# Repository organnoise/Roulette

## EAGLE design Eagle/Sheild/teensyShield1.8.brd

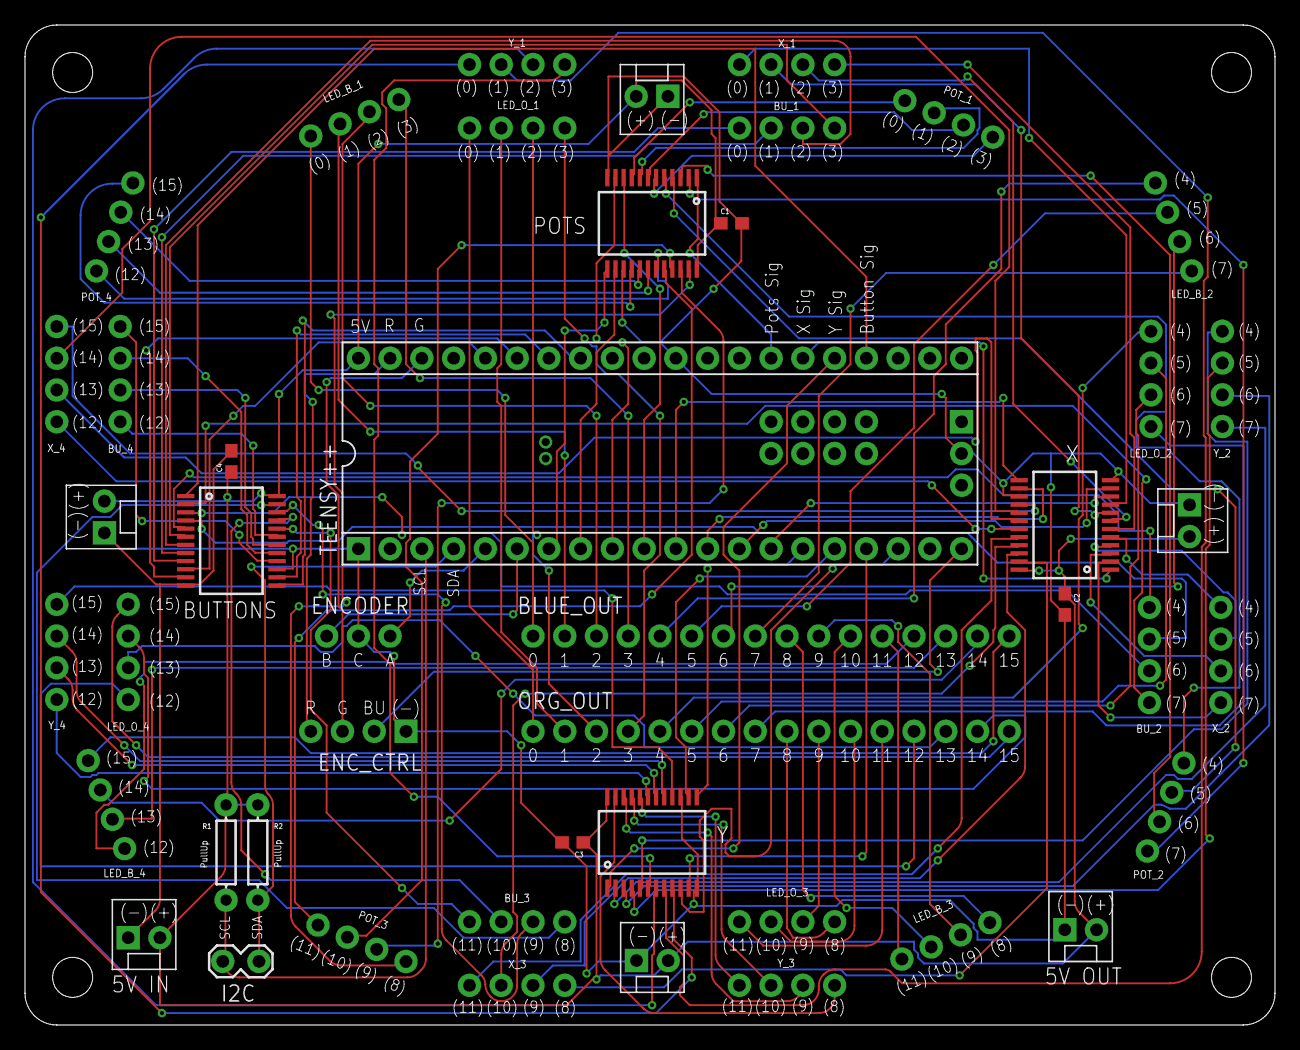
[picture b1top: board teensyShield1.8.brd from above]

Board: 2 copper layers, 100.0 x 80.0 mm, 46 parts (0 on the bottom side), 125 nets.

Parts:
BLUE_OUT: 1X16_NO_SILK
BUTTONS: MUX-74HC4067; SSOP24
BU_1, BU_2, BU_3, BU_4: 1X04_NO_SILK_ALL_ROUND
C1, C2, C3, C4: 0.1uF; 0603
ENCODER: 1X03_NO_SILK
ENC_CTRL: 1X04_NO_SILK
I2C: 1X02_LOCK
LED_B_1, LED_B_2, LED_B_3, LED_B_4: 1X04_NO_SILK_ALL_ROUND
LED_O_1, LED_O_2, LED_O_3, LED_O_4: 1X04_NO_SILK_ALL_ROUND
ORG_OUT: 1X16_NO_SILK
POTS: MUX-74HC4067; SSOP24
POT_1, POT_2, POT_3, POT_4: 1X04_NO_SILK_ALL_ROUND
POW_1, POW_2, POW_3, POW_4: MOLEX-1X2
POW_IN: MOLEX-1X2
POW_OUT: MOLEX-1X2
R1, R2: PullUp; AXIAL-0.3
TEENSY++: ARDUINO-TEENSY++; TEENSY++
X: MUX-74HC4067; SSOP24
X_1, X_2, X_3, X_4: 1X04_NO_SILK_ALL_ROUND
Y: MUX-74HC4067; SSOP24
Y_1, Y_2, Y_3, Y_4: 1X04_NO_SILK_ALL_ROUND

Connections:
5V: BUTTONS.24, C1.1, C2.1, C3.1, C4.1, POTS.24, POW_1.2, POW_2.2, POW_3.2, POW_4.2, POW_IN.2, POW_OUT.2, R1.P$2, R2.P$1, TEENSY++.+5V, X.24, Y.24
BU_C0: BUTTONS.9, BU_1.1
BU_C1: BUTTONS.8, BU_1.2
BU_C2: BUTTONS.7, BU_1.3
BU_C3: BUTTONS.6, BU_1.4
BU_C4: BUTTONS.5, BU_2.1
BU_C5: BUTTONS.4, BU_2.2
BU_C6: BUTTONS.3, BU_2.3
BU_C7: BUTTONS.2, BU_2.4
BU_C8: BUTTONS.23, BU_3.1
BU_C9: BUTTONS.22, BU_3.2
BU_C10: BUTTONS.21, BU_3.3
BU_C11: BUTTONS.20, BU_3.4
BU_C12: BUTTONS.19, BU_4.1
BU_C13: BUTTONS.18, BU_4.2
BU_C14: BUTTONS.17, BU_4.3
BU_C15: BUTTONS.16, BU_4.4
ENC_1: ENCODER.3, TEENSY++.D2
ENC_2: ENCODER.1, TEENSY++.D3
ENC_BU: ENC_CTRL.2, TEENSY++.C7
ENC_G: ENC_CTRL.3, TEENSY++.B5
ENC_R: ENC_CTRL.4, TEENSY++.B6
GND: BUTTONS.12, BUTTONS.15, C1.2, C2.2, C3.2, C4.2, ENCODER.2, ENC_CTRL.1, POTS.12, POTS.15, POW_1.1, POW_2.1, POW_3.1, POW_4.1, POW_IN.1, POW_OUT.1, TEENSY++.GND, TEENSY++.GND2, TEENSY++.GRND1, X.12, X.15, Y.12, Y.15
LED_B_C0: BLUE_OUT.1, LED_B_1.1
LED_B_C1: BLUE_OUT.2, LED_B_1.2
LED_B_C2: BLUE_OUT.3, LED_B_1.3
LED_B_C3: BLUE_OUT.4, LED_B_1.4
LED_B_C4: BLUE_OUT.5, LED_B_2.1
LED_B_C5: BLUE_OUT.6, LED_B_2.2
LED_B_C6: BLUE_OUT.7, LED_B_2.3
LED_B_C7: BLUE_OUT.8, LED_B_2.4
LED_B_C8: BLUE_OUT.9, LED_B_3.1
LED_B_C9: BLUE_OUT.10, LED_B_3.2
LED_B_C10: BLUE_OUT.11, LED_B_3.3
LED_B_C11: BLUE_OUT.12, LED_B_3.4
LED_B_C12: BLUE_OUT.13, LED_B_4.1
LED_B_C13: BLUE_OUT.14, LED_B_4.2
LED_B_C14: BLUE_OUT.15, LED_B_4.3
LED_B_C15: BLUE_OUT.16, LED_B_4.4
LED_O_C0: LED_O_1.1, ORG_OUT.1
LED_O_C1: LED_O_1.2, ORG_OUT.2
LED_O_C2: LED_O_1.3, ORG_OUT.3
LED_O_C3: LED_O_1.4, ORG_OUT.4
LED_O_C4: LED_O_2.1, ORG_OUT.5
LED_O_C5: LED_O_2.2, ORG_OUT.6
LED_O_C6: LED_O_2.3, ORG_OUT.7
LED_O_C7: LED_O_2.4, ORG_OUT.8
LED_O_C8: LED_O_3.1, ORG_OUT.9
LED_O_C9: LED_O_3.2, ORG_OUT.10
LED_O_C10: LED_O_3.3, ORG_OUT.11
LED_O_C11: LED_O_3.4, ORG_OUT.12
LED_O_C12: LED_O_4.1, ORG_OUT.13
LED_O_C13: LED_O_4.2, ORG_OUT.14
LED_O_C14: LED_O_4.3, ORG_OUT.15
LED_O_C15: LED_O_4.4, ORG_OUT.16
MUX1_S0: POTS.10, TEENSY++.D7
MUX1_S1: POTS.11, TEENSY++.D6
MUX1_S2: POTS.14, TEENSY++.D5
MUX1_S3: POTS.13, TEENSY++.D4
MUX1_SIG: POTS.1, TEENSY++.F1
MUX2_S0: TEENSY++.C1, X.10
MUX2_S1: TEENSY++.C0, X.11
MUX2_S2: TEENSY++.E1, X.14
MUX2_S3: TEENSY++.E0, X.13
MUX2_SIG: TEENSY++.F2, X.1
MUX3_S0: TEENSY++.C5, Y.10
MUX3_S1: TEENSY++.C4, Y.11
MUX3_S2: TEENSY++.C3, Y.14
MUX3_S3: TEENSY++.C2, Y.13
MUX3_SIG: TEENSY++.F3, Y.1
MUX4_S0: BUTTONS.10, TEENSY++.B3
MUX4_S1: BUTTONS.11, TEENSY++.B2
MUX4_S2: BUTTONS.14, TEENSY++.B1
MUX4_S3: BUTTONS.13, TEENSY++.B0
MUX4_SIG: BUTTONS.1, TEENSY++.F4
POT_C0: POTS.9, POT_1.1
POT_C1: POTS.8, POT_1.2
POT_C2: POTS.7, POT_1.3
POT_C3: POTS.6, POT_1.4
POT_C4: POTS.5, POT_2.1
POT_C5: POTS.4, POT_2.2
POT_C6: POTS.3, POT_2.3
POT_C7: POTS.2, POT_2.4
POT_C8: POTS.23, POT_3.1
POT_C9: POTS.22, POT_3.2
POT_C10: POTS.21, POT_3.3
POT_C11: POTS.20, POT_3.4
POT_C12: POTS.19, POT_4.1
POT_C13: POTS.18, POT_4.2
POT_C14: POTS.17, POT_4.3
POT_C15: POTS.16, POT_4.4
SCL: I2C.2, R1.P$1, TEENSY++.D0
SDA: I2C.1, R2.P$2, TEENSY++.D1
X_C0: X.9, X_1.1
X_C1: X.8, X_1.2
X_C2: X.7, X_1.3
X_C3: X.6, X_1.4
X_C4: X.5, X_2.1
X_C5: X.4, X_2.2
X_C6: X.3, X_2.3
X_C7: X.2, X_2.4
X_C8: X.23, X_3.1
X_C9: X.22, X_3.2
X_C10: X.21, X_3.3
X_C11: X.20, X_3.4
X_C12: X.19, X_4.1
X_C13: X.18, X_4.2
X_C14: X.17, X_4.3
X_C15: X.16, X_4.4
Y_C0: Y.9, Y_1.1
Y_C1: Y.8, Y_1.2
Y_C2: Y.7, Y_1.3
Y_C3: Y.6, Y_1.4
Y_C4: Y.5, Y_2.1
Y_C5: Y.4, Y_2.2
Y_C6: Y.3, Y_2.3
Y_C7: Y.2, Y_2.4
Y_C8: Y.23, Y_3.1
Y_C9: Y.22, Y_3.2
Y_C10: Y.21, Y_3.3
Y_C11: Y.20, Y_3.4
Y_C12: Y.19, Y_4.1
Y_C13: Y.18, Y_4.2
Y_C14: Y.17, Y_4.3
Y_C15: Y.16, Y_4.4

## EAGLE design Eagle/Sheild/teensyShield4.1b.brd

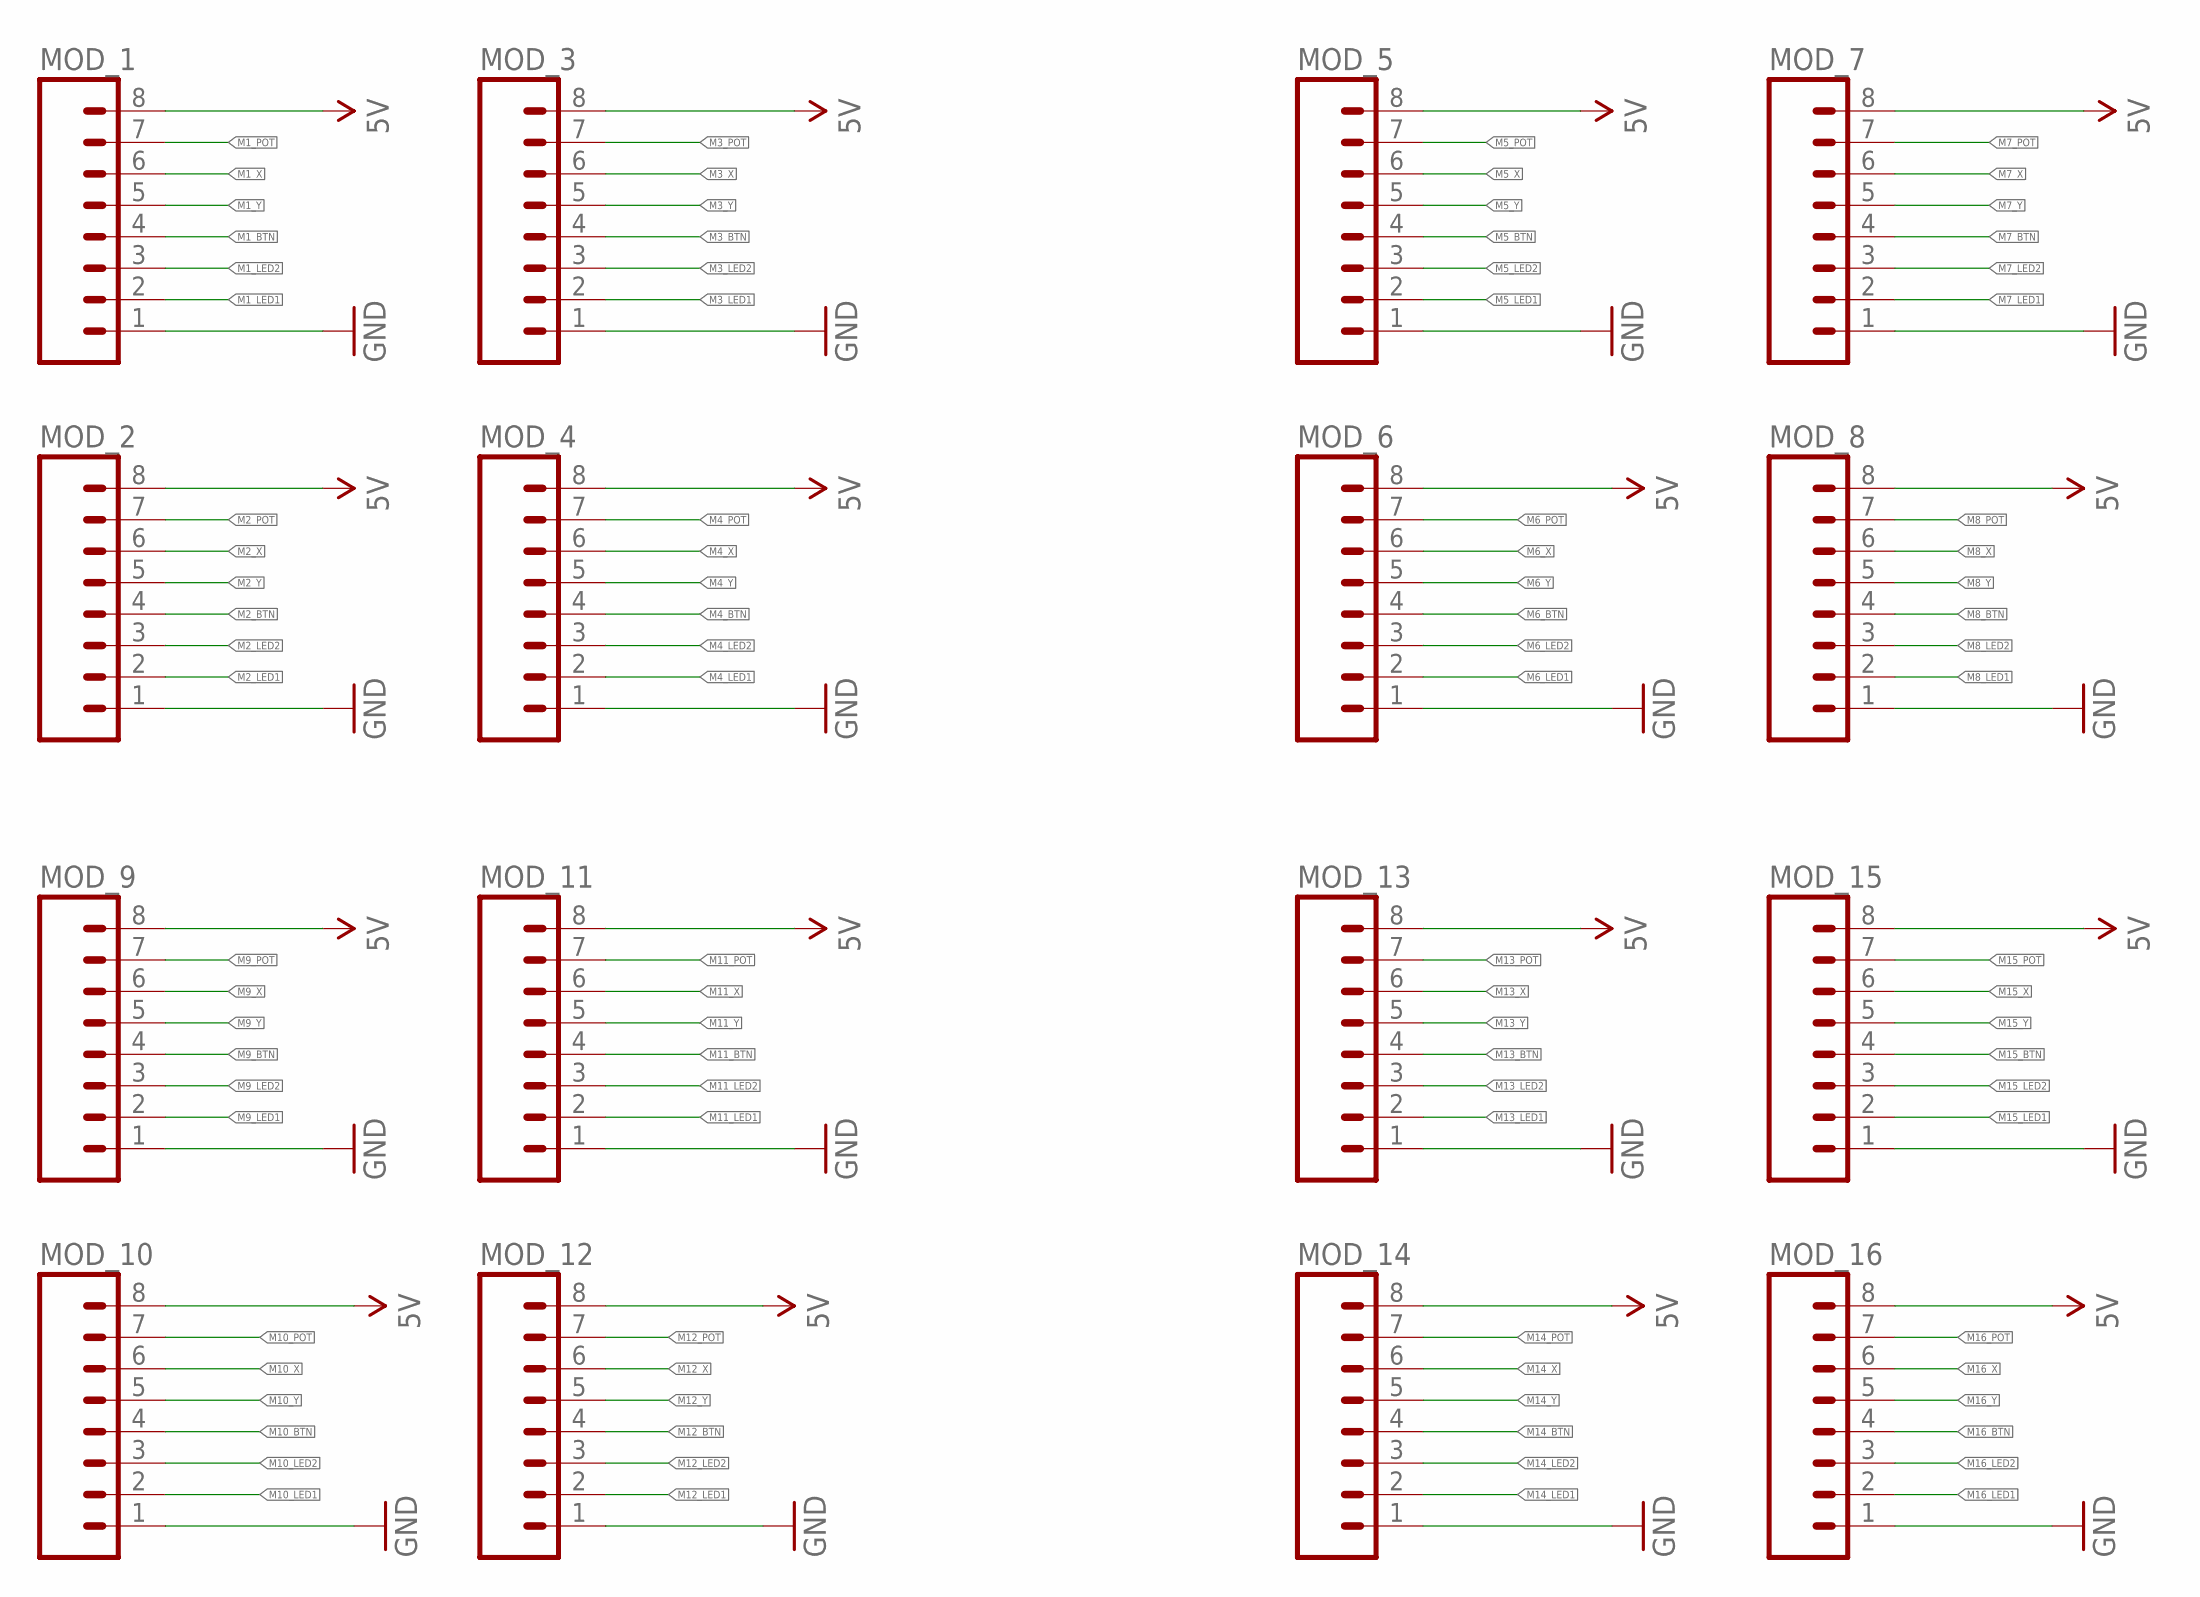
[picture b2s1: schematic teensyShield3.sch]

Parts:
MOD_1, MOD_2, MOD_3, MOD_4, MOD_5, MOD_6, MOD_7, MOD_8, MOD_9, MOD_10, MOD_11, MOD_12, MOD_13, MOD_14, MOD_15, MOD_16: M08; 1X08_ROUND

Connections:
5V: MOD_1.8, MOD_2.8, MOD_3.8, MOD_4.8, MOD_5.8, MOD_6.8, MOD_7.8, MOD_8.8, MOD_9.8, MOD_10.8, MOD_11.8, MOD_12.8, MOD_13.8, MOD_14.8, MOD_15.8, MOD_16.8; also elsewhere on the board
GND: MOD_1.1, MOD_2.1, MOD_3.1, MOD_4.1, MOD_5.1, MOD_6.1, MOD_7.1, MOD_8.1, MOD_9.1, MOD_10.1, MOD_11.1, MOD_12.1, MOD_13.1, MOD_14.1, MOD_15.1, MOD_16.1; also elsewhere on the board
M1_BTN: MOD_1.4; also elsewhere on the board
M1_LED1: MOD_1.2; also elsewhere on the board
M1_LED2: MOD_1.3; also elsewhere on the board
M1_POT: MOD_1.7; also elsewhere on the board
M1_X: MOD_1.6; also elsewhere on the board
M1_Y: MOD_1.5; also elsewhere on the board
M2_BTN: MOD_2.4; also elsewhere on the board
M2_LED1: MOD_2.2; also elsewhere on the board
M2_LED2: MOD_2.3; also elsewhere on the board
M2_POT: MOD_2.7; also elsewhere on the board
M2_X: MOD_2.6; also elsewhere on the board
M2_Y: MOD_2.5; also elsewhere on the board
M3_BTN: MOD_3.4; also elsewhere on the board
M3_LED1: MOD_3.2; also elsewhere on the board
M3_LED2: MOD_3.3; also elsewhere on the board
M3_POT: MOD_3.7; also elsewhere on the board
M3_X: MOD_3.6; also elsewhere on the board
M3_Y: MOD_3.5; also elsewhere on the board
M4_BTN: MOD_4.4; also elsewhere on the board
M4_LED1: MOD_4.2; also elsewhere on the board
M4_LED2: MOD_4.3; also elsewhere on the board
M4_POT: MOD_4.7; also elsewhere on the board
M4_X: MOD_4.6; also elsewhere on the board
M4_Y: MOD_4.5; also elsewhere on the board
M5_BTN: MOD_5.4; also elsewhere on the board
M5_LED1: MOD_5.2; also elsewhere on the board
M5_LED2: MOD_5.3; also elsewhere on the board
M5_POT: MOD_5.7; also elsewhere on the board
M5_X: MOD_5.6; also elsewhere on the board
M5_Y: MOD_5.5; also elsewhere on the board
M6_BTN: MOD_6.4; also elsewhere on the board
M6_LED1: MOD_6.2; also elsewhere on the board
M6_LED2: MOD_6.3; also elsewhere on the board
M6_POT: MOD_6.7; also elsewhere on the board
M6_X: MOD_6.6; also elsewhere on the board
M6_Y: MOD_6.5; also elsewhere on the board
M7_BTN: MOD_7.4; also elsewhere on the board
M7_LED1: MOD_7.2; also elsewhere on the board
M7_LED2: MOD_7.3; also elsewhere on the board
M7_POT: MOD_7.7; also elsewhere on the board
M7_X: MOD_7.6; also elsewhere on the board
M7_Y: MOD_7.5; also elsewhere on the board
M8_BTN: MOD_8.4; also elsewhere on the board
M8_LED1: MOD_8.2; also elsewhere on the board
M8_LED2: MOD_8.3; also elsewhere on the board
M8_POT: MOD_8.7; also elsewhere on the board
M8_X: MOD_8.6; also elsewhere on the board
M8_Y: MOD_8.5; also elsewhere on the board
M9_BTN: MOD_9.4; also elsewhere on the board
M9_LED1: MOD_9.2; also elsewhere on the board
M9_LED2: MOD_9.3; also elsewhere on the board
M9_POT: MOD_9.7; also elsewhere on the board
M9_X: MOD_9.6; also elsewhere on the board
M9_Y: MOD_9.5; also elsewhere on the board
M10_BTN: MOD_10.4; also elsewhere on the board
M10_LED1: MOD_10.2; also elsewhere on the board
M10_LED2: MOD_10.3; also elsewhere on the board
M10_POT: MOD_10.7; also elsewhere on the board
M10_X: MOD_10.6; also elsewhere on the board
M10_Y: MOD_10.5; also elsewhere on the board
M11_BTN: MOD_11.4; also elsewhere on the board
M11_LED1: MOD_11.2; also elsewhere on the board
M11_LED2: MOD_11.3; also elsewhere on the board
M11_POT: MOD_11.7; also elsewhere on the board
M11_X: MOD_11.6; also elsewhere on the board
M11_Y: MOD_11.5; also elsewhere on the board
M12_BTN: MOD_12.4; also elsewhere on the board
M12_LED1: MOD_12.2; also elsewhere on the board
M12_LED2: MOD_12.3; also elsewhere on the board
M12_POT: MOD_12.7; also elsewhere on the board
M12_X: MOD_12.6; also elsewhere on the board
M12_Y: MOD_12.5; also elsewhere on the board
M13_BTN: MOD_13.4; also elsewhere on the board
M13_LED1: MOD_13.2; also elsewhere on the board
M13_LED2: MOD_13.3; also elsewhere on the board
M13_POT: MOD_13.7; also elsewhere on the board
M13_X: MOD_13.6; also elsewhere on the board
M13_Y: MOD_13.5; also elsewhere on the board
M14_BTN: MOD_14.4; also elsewhere on the board
M14_LED1: MOD_14.2; also elsewhere on the board
M14_LED2: MOD_14.3; also elsewhere on the board
M14_POT: MOD_14.7; also elsewhere on the board
M14_X: MOD_14.6; also elsewhere on the board
M14_Y: MOD_14.5; also elsewhere on the board
M15_BTN: MOD_15.4; also elsewhere on the board
M15_LED1: MOD_15.2; also elsewhere on the board
M15_LED2: MOD_15.3; also elsewhere on the board
M15_POT: MOD_15.7; also elsewhere on the board
M15_X: MOD_15.6; also elsewhere on the board
M15_Y: MOD_15.5; also elsewhere on the board
M16_BTN: MOD_16.4; also elsewhere on the board
M16_LED1: MOD_16.2; also elsewhere on the board
M16_LED2: MOD_16.3; also elsewhere on the board
M16_POT: MOD_16.7; also elsewhere on the board
M16_X: MOD_16.6; also elsewhere on the board
M16_Y: MOD_16.5; also elsewhere on the board

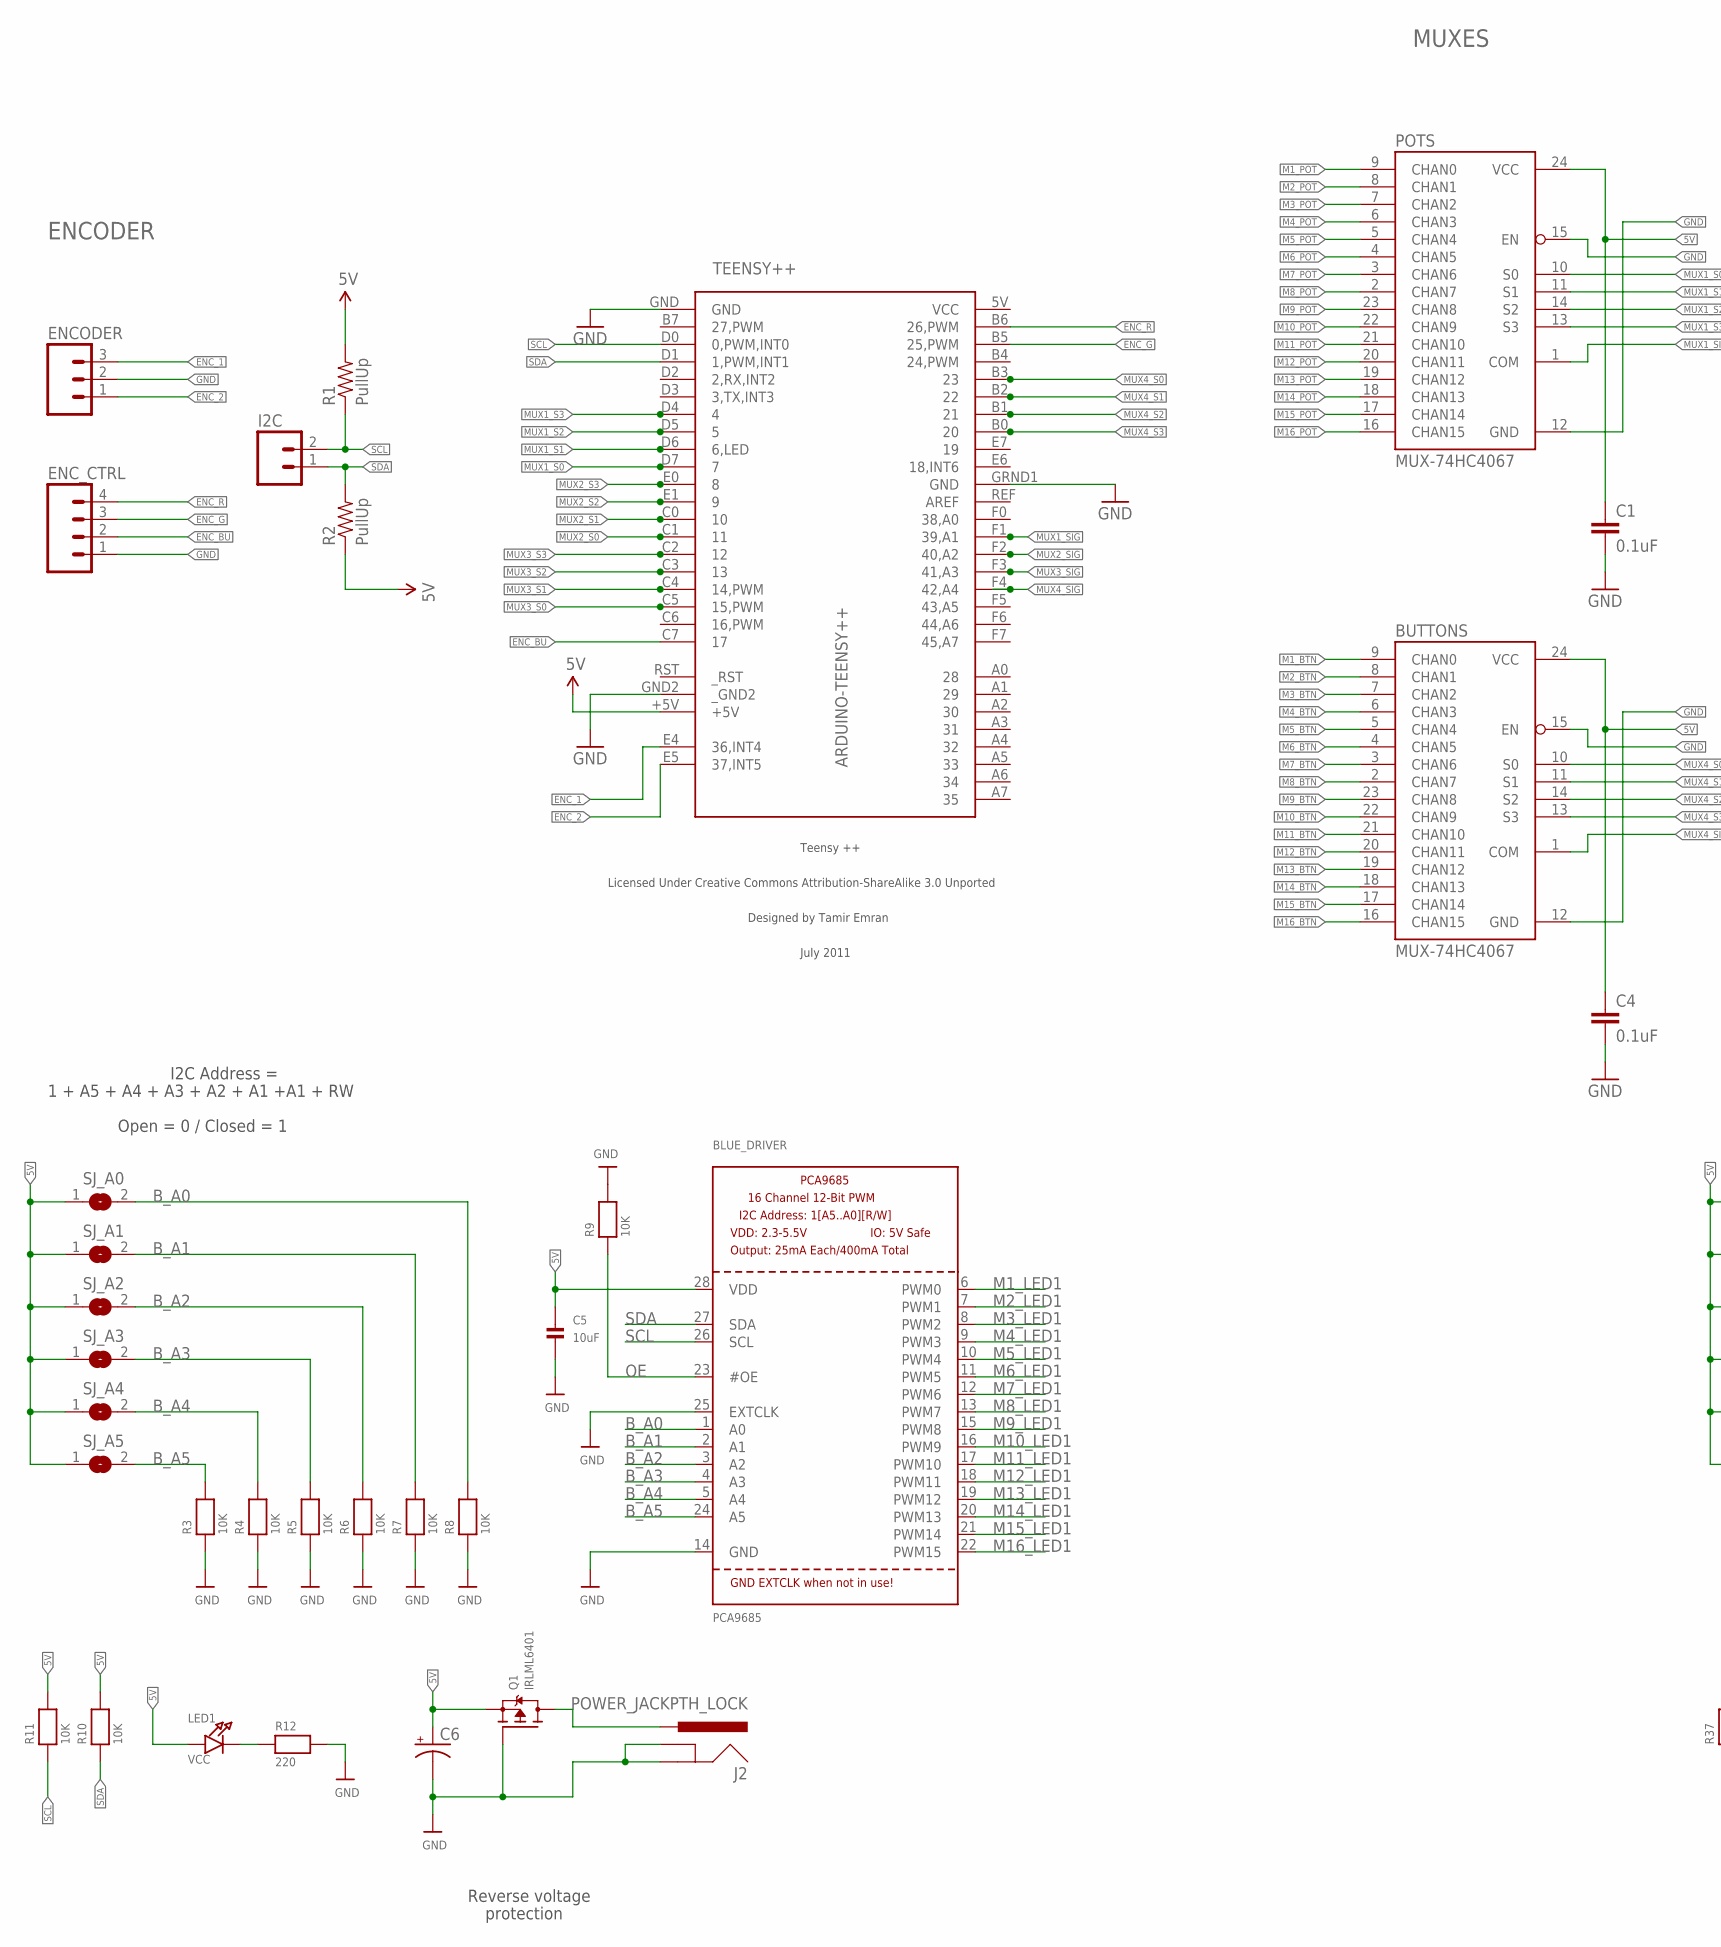
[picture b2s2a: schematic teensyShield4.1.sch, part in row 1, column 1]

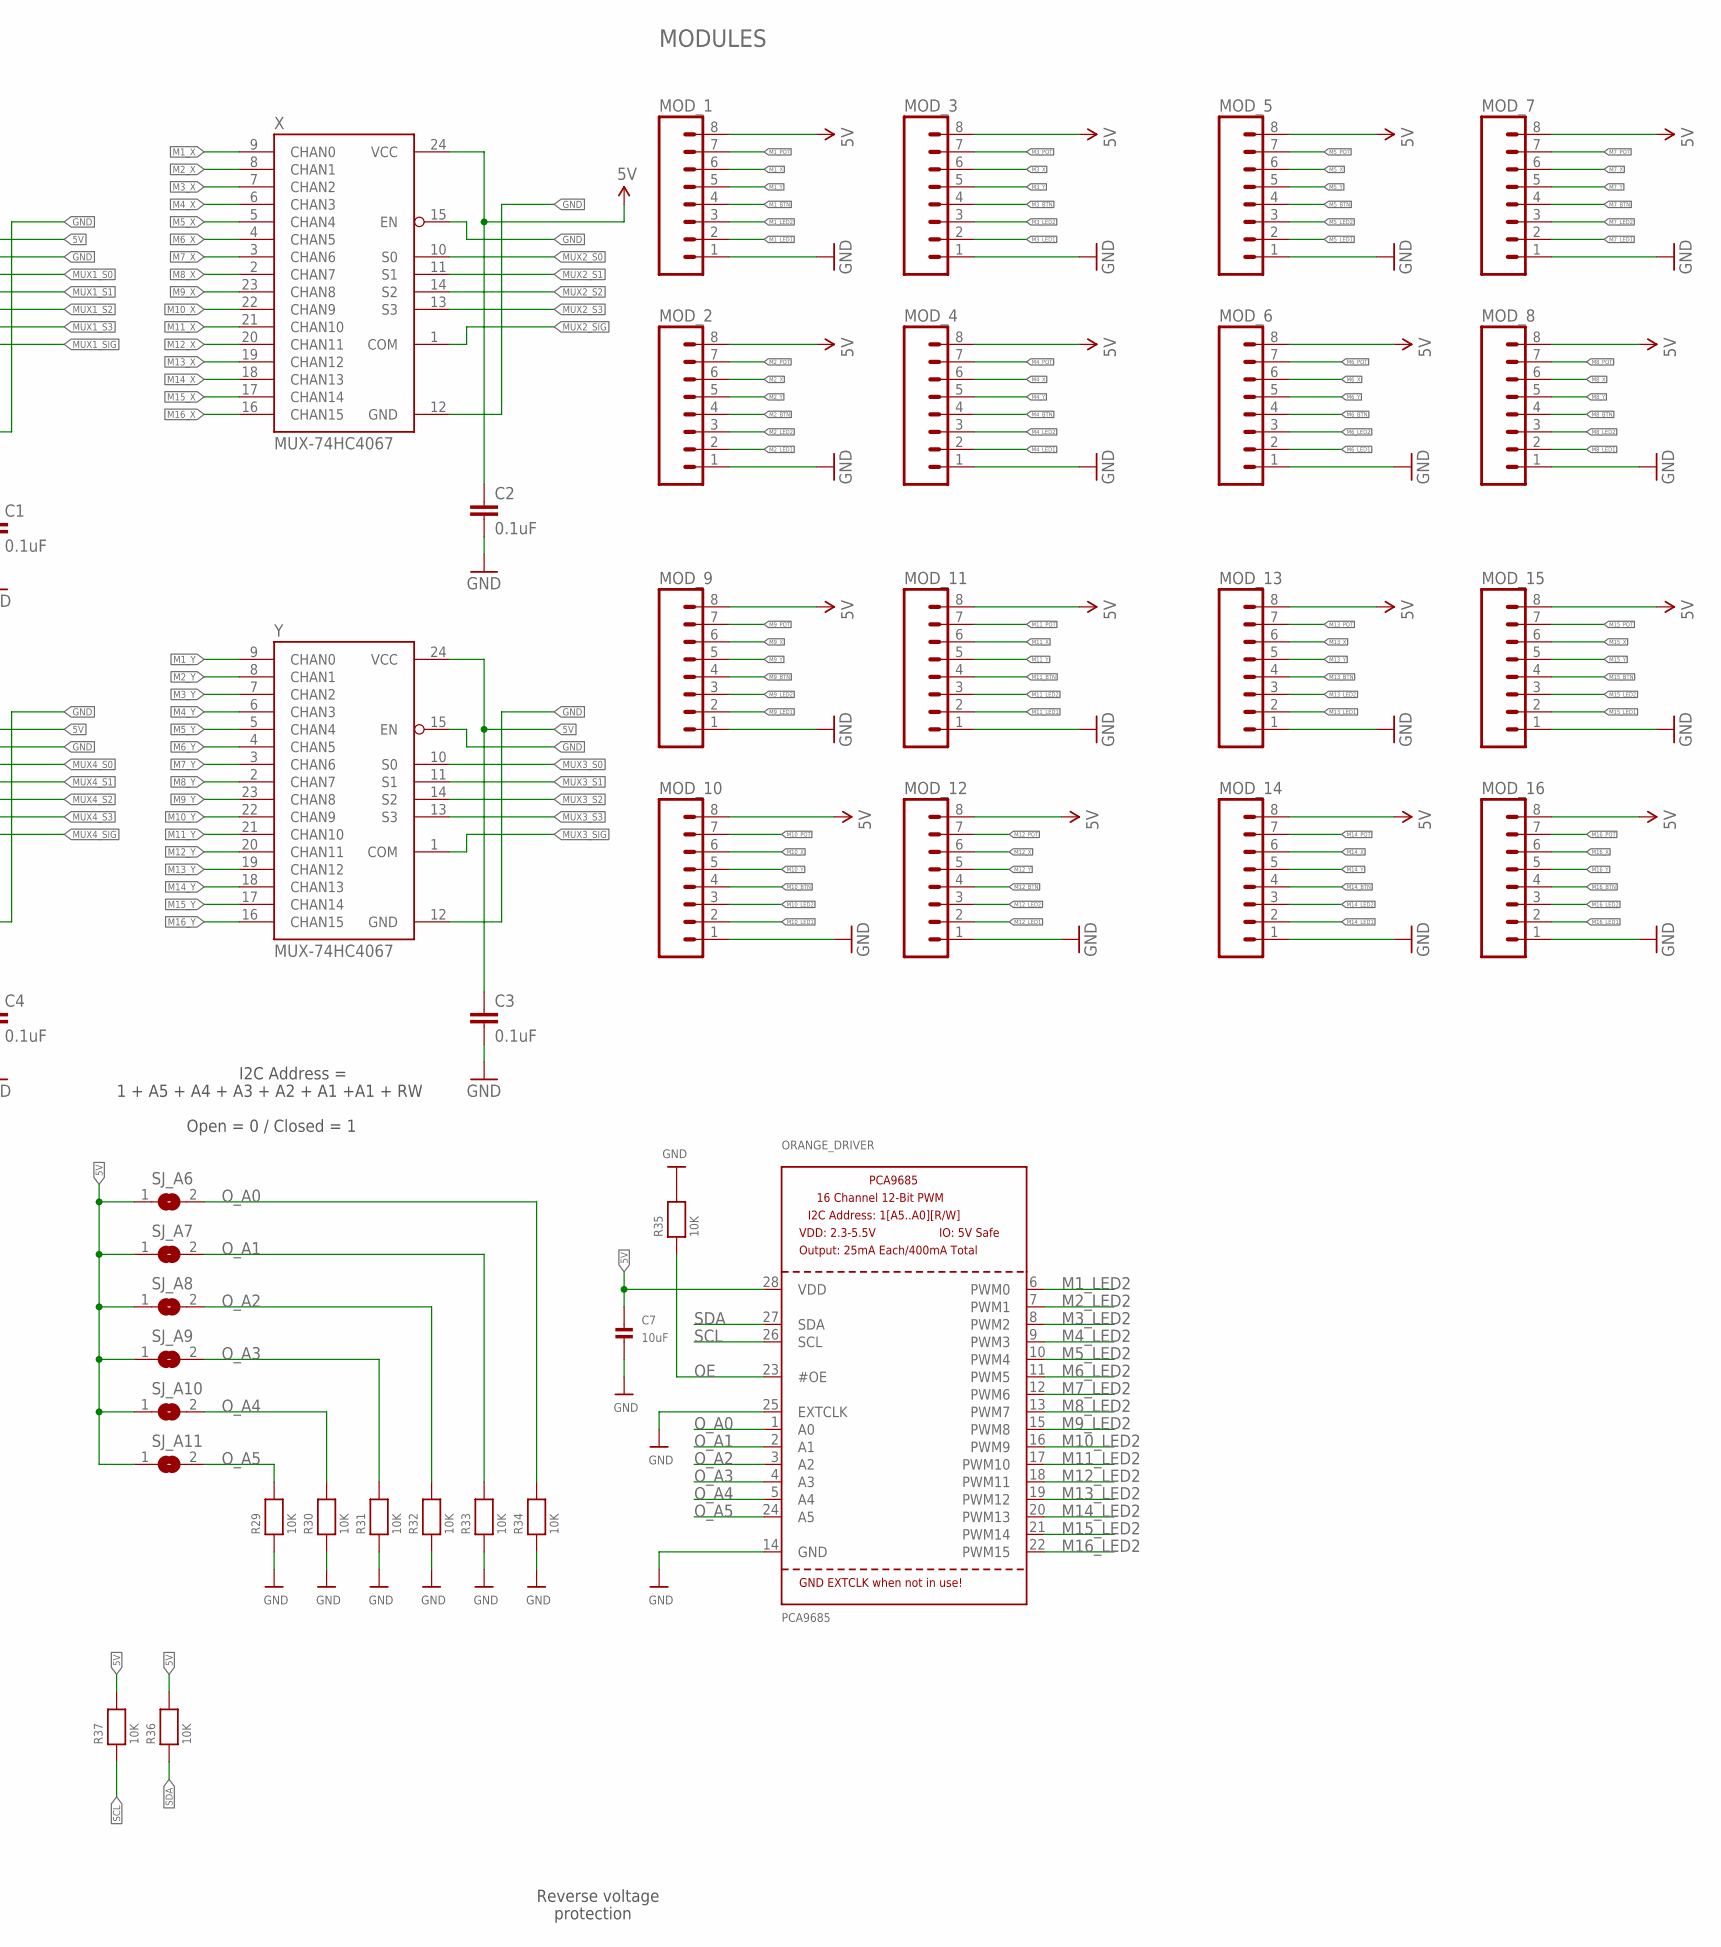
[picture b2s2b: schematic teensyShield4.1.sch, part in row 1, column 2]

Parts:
BLUE_DRIVER: PCA9685; TSSOP28
BUTTONS: MUX-74HC4067; SSOP24
C1, C2, C3, C4: 0.1uF; 0603
C5, C7: 10uF; 0805
C6: CPOL-USE3.5-8; E3,5-8
ENCODER: M031X03_NO_SILK; 1X03_NO_SILK
ENC_CTRL: M041X04_NO_SILK; 1X04_NO_SILK
I2C: M02LOCK; 1X02_LOCK
J2: POWER_JACKPTH_LOCK; POWER_JACK_PTH_LOCK
LED1: VCC; CHIPLED_0805
MOD_1, MOD_2, MOD_3, MOD_4, MOD_5, MOD_6, MOD_7, MOD_8, MOD_9, MOD_10, MOD_11, MOD_12, MOD_13, MOD_14, MOD_15, MOD_16: M08; 1X08_ROUND
ORANGE_DRIVER: PCA9685; TSSOP28
POTS: MUX-74HC4067; SSOP24
Q1: IRLML6401; SOT23-WIDE
R1, R2: PullUp; AXIAL-0.3
R3, R4, R5, R6, R7, R8, R9, R10, R11, R29, R30, R31, R32, R33, R34, R35, R36, R37: 10K; 0805
R12: 220; 0805
SJ_A0, SJ_A1, SJ_A2, SJ_A3, SJ_A4, SJ_A5, SJ_A6, SJ_A7, SJ_A8, SJ_A9, SJ_A10, SJ_A11: SOLDERJUMPERREFLOW_NOPASTE; SOLDERJUMPER_REFLOW_NOPASTE
TEENSY++: ARDUINO-TEENSY++; TEENSY++
X: MUX-74HC4067; SSOP24
Y: MUX-74HC4067; SSOP24

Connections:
5V: BLUE_DRIVER.28 (VDD), BUTTONS.24 (VCC), C1.1, C2.1, C3.1, C4.1, C5.1, C6.+, C7.1, LED1.A, MOD_1.8, MOD_2.8, MOD_3.8, MOD_4.8, MOD_5.8, MOD_6.8, MOD_7.8, MOD_8.8, MOD_9.8, MOD_10.8, MOD_11.8, MOD_12.8, MOD_13.8, MOD_14.8, MOD_15.8, MOD_16.8, ORANGE_DRIVER.28 (VDD), POTS.24 (VCC), Q1.2 (S), R1.P$2 (2), R2.P$1 (1), R10.2, R11.2, R36.2, R37.2, SJ_A0.1, SJ_A1.1, SJ_A2.1, SJ_A3.1, SJ_A4.1, SJ_A5.1, SJ_A6.1, SJ_A7.1, SJ_A8.1, SJ_A9.1, SJ_A10.1, SJ_A11.1, TEENSY++.+5V, X.24 (VCC), Y.24 (VCC)
B_A0: BLUE_DRIVER.1 (A0), R8.2, SJ_A0.2
B_A1: BLUE_DRIVER.2 (A1), R7.2, SJ_A1.2
B_A2: BLUE_DRIVER.3 (A2), R6.2, SJ_A2.2
B_A3: BLUE_DRIVER.4 (A3), R5.2, SJ_A3.2
B_A4: BLUE_DRIVER.5 (A4), R4.2, SJ_A4.2
B_A5: BLUE_DRIVER.24 (A5), R3.2, SJ_A5.2
ENC_1: ENCODER.3, TEENSY++.E4 (36,INT4)
ENC_2: ENCODER.1, TEENSY++.E5 (37,INT5)
ENC_BU: ENC_CTRL.2, TEENSY++.C7 (17)
ENC_G: ENC_CTRL.3, TEENSY++.B5 (25,PWM)
ENC_R: ENC_CTRL.4, TEENSY++.B6 (26,PWM)
GND: BLUE_DRIVER.14 (GND), BLUE_DRIVER.25 (EXTCLK), BUTTONS.12 (GND), BUTTONS.15 (EN), C1.2, C2.2, C3.2, C4.2, C5.2, C6.-, C7.2, ENCODER.2, ENC_CTRL.1, J2.GND, J2.GNDBREAK, MOD_1.1, MOD_2.1, MOD_3.1, MOD_4.1, MOD_5.1, MOD_6.1, MOD_7.1, MOD_8.1, MOD_9.1, MOD_10.1, MOD_11.1, MOD_12.1, MOD_13.1, MOD_14.1, MOD_15.1, MOD_16.1, ORANGE_DRIVER.14 (GND), ORANGE_DRIVER.25 (EXTCLK), POTS.12 (GND), POTS.15 (EN), Q1.1 (G), R3.1, R4.1, R5.1, R6.1, R7.1, R8.1, R9.2, R12.2, R29.1, R30.1, R31.1, R32.1, R33.1, R34.1, R35.2, TEENSY++.GND, TEENSY++.GND2 (_GND2), TEENSY++.GRND1 (GND), X.12 (GND), X.15 (EN), Y.12 (GND), Y.15 (EN)
M1_BTN: BUTTONS.9 (CHAN0), MOD_1.4
M1_LED1: BLUE_DRIVER.6 (PWM0), MOD_1.2
M1_LED2: MOD_1.3, ORANGE_DRIVER.6 (PWM0)
M1_POT: MOD_1.7, POTS.9 (CHAN0)
M1_X: MOD_1.6, X.9 (CHAN0)
M1_Y: MOD_1.5, Y.9 (CHAN0)
M2_BTN: BUTTONS.8 (CHAN1), MOD_2.4
M2_LED1: BLUE_DRIVER.7 (PWM1), MOD_2.2
M2_LED2: MOD_2.3, ORANGE_DRIVER.7 (PWM1)
M2_POT: MOD_2.7, POTS.8 (CHAN1)
M2_X: MOD_2.6, X.8 (CHAN1)
M2_Y: MOD_2.5, Y.8 (CHAN1)
M3_BTN: BUTTONS.7 (CHAN2), MOD_3.4
M3_LED1: BLUE_DRIVER.8 (PWM2), MOD_3.2
M3_LED2: MOD_3.3, ORANGE_DRIVER.8 (PWM2)
M3_POT: MOD_3.7, POTS.7 (CHAN2)
M3_X: MOD_3.6, X.7 (CHAN2)
M3_Y: MOD_3.5, Y.7 (CHAN2)
M4_BTN: BUTTONS.6 (CHAN3), MOD_4.4
M4_LED1: BLUE_DRIVER.9 (PWM3), MOD_4.2
M4_LED2: MOD_4.3, ORANGE_DRIVER.9 (PWM3)
M4_POT: MOD_4.7, POTS.6 (CHAN3)
M4_X: MOD_4.6, X.6 (CHAN3)
M4_Y: MOD_4.5, Y.6 (CHAN3)
M5_BTN: BUTTONS.5 (CHAN4), MOD_5.4
M5_LED1: BLUE_DRIVER.10 (PWM4), MOD_5.2
M5_LED2: MOD_5.3, ORANGE_DRIVER.10 (PWM4)
M5_POT: MOD_5.7, POTS.5 (CHAN4)
M5_X: MOD_5.6, X.5 (CHAN4)
M5_Y: MOD_5.5, Y.5 (CHAN4)
M6_BTN: BUTTONS.4 (CHAN5), MOD_6.4
M6_LED1: BLUE_DRIVER.11 (PWM5), MOD_6.2
M6_LED2: MOD_6.3, ORANGE_DRIVER.11 (PWM5)
M6_POT: MOD_6.7, POTS.4 (CHAN5)
M6_X: MOD_6.6, X.4 (CHAN5)
M6_Y: MOD_6.5, Y.4 (CHAN5)
M7_BTN: BUTTONS.3 (CHAN6), MOD_7.4
M7_LED1: BLUE_DRIVER.12 (PWM6), MOD_7.2
M7_LED2: MOD_7.3, ORANGE_DRIVER.12 (PWM6)
M7_POT: MOD_7.7, POTS.3 (CHAN6)
M7_X: MOD_7.6, X.3 (CHAN6)
M7_Y: MOD_7.5, Y.3 (CHAN6)
M8_BTN: BUTTONS.2 (CHAN7), MOD_8.4
M8_LED1: BLUE_DRIVER.13 (PWM7), MOD_8.2
M8_LED2: MOD_8.3, ORANGE_DRIVER.13 (PWM7)
M8_POT: MOD_8.7, POTS.2 (CHAN7)
M8_X: MOD_8.6, X.2 (CHAN7)
M8_Y: MOD_8.5, Y.2 (CHAN7)
M9_BTN: BUTTONS.23 (CHAN8), MOD_9.4
M9_LED1: BLUE_DRIVER.15 (PWM8), MOD_9.2
M9_LED2: MOD_9.3, ORANGE_DRIVER.15 (PWM8)
M9_POT: MOD_9.7, POTS.23 (CHAN8)
M9_X: MOD_9.6, X.23 (CHAN8)
M9_Y: MOD_9.5, Y.23 (CHAN8)
M10_BTN: BUTTONS.22 (CHAN9), MOD_10.4
M10_LED1: BLUE_DRIVER.16 (PWM9), MOD_10.2
M10_LED2: MOD_10.3, ORANGE_DRIVER.16 (PWM9)
M10_POT: MOD_10.7, POTS.22 (CHAN9)
M10_X: MOD_10.6, X.22 (CHAN9)
M10_Y: MOD_10.5, Y.22 (CHAN9)
M11_BTN: BUTTONS.21 (CHAN10), MOD_11.4
M11_LED1: BLUE_DRIVER.17 (PWM10), MOD_11.2
M11_LED2: MOD_11.3, ORANGE_DRIVER.17 (PWM10)
M11_POT: MOD_11.7, POTS.21 (CHAN10)
M11_X: MOD_11.6, X.21 (CHAN10)
M11_Y: MOD_11.5, Y.21 (CHAN10)
M12_BTN: BUTTONS.20 (CHAN11), MOD_12.4
M12_LED1: BLUE_DRIVER.18 (PWM11), MOD_12.2
M12_LED2: MOD_12.3, ORANGE_DRIVER.18 (PWM11)
M12_POT: MOD_12.7, POTS.20 (CHAN11)
M12_X: MOD_12.6, X.20 (CHAN11)
M12_Y: MOD_12.5, Y.20 (CHAN11)
M13_BTN: BUTTONS.19 (CHAN12), MOD_13.4
M13_LED1: BLUE_DRIVER.19 (PWM12), MOD_13.2
M13_LED2: MOD_13.3, ORANGE_DRIVER.19 (PWM12)
M13_POT: MOD_13.7, POTS.19 (CHAN12)
M13_X: MOD_13.6, X.19 (CHAN12)
M13_Y: MOD_13.5, Y.19 (CHAN12)
M14_BTN: BUTTONS.18 (CHAN13), MOD_14.4
M14_LED1: BLUE_DRIVER.20 (PWM13), MOD_14.2
M14_LED2: MOD_14.3, ORANGE_DRIVER.20 (PWM13)
M14_POT: MOD_14.7, POTS.18 (CHAN13)
M14_X: MOD_14.6, X.18 (CHAN13)
M14_Y: MOD_14.5, Y.18 (CHAN13)
M15_BTN: BUTTONS.17 (CHAN14), MOD_15.4
M15_LED1: BLUE_DRIVER.21 (PWM14), MOD_15.2
M15_LED2: MOD_15.3, ORANGE_DRIVER.21 (PWM14)
M15_POT: MOD_15.7, POTS.17 (CHAN14)
M15_X: MOD_15.6, X.17 (CHAN14)
M15_Y: MOD_15.5, Y.17 (CHAN14)
M16_BTN: BUTTONS.16 (CHAN15), MOD_16.4
M16_LED1: BLUE_DRIVER.22 (PWM15), MOD_16.2
M16_LED2: MOD_16.3, ORANGE_DRIVER.22 (PWM15)
M16_POT: MOD_16.7, POTS.16 (CHAN15)
M16_X: MOD_16.6, X.16 (CHAN15)
M16_Y: MOD_16.5, Y.16 (CHAN15)
MUX1_S0: POTS.10 (S0), TEENSY++.D7 (7)
MUX1_S1: POTS.11 (S1), TEENSY++.D6 (6,LED)
MUX1_S2: POTS.14 (S2), TEENSY++.D5 (5)
MUX1_S3: POTS.13 (S3), TEENSY++.D4 (4)
MUX1_SIG: POTS.1 (COM), TEENSY++.F1 (39,A1)
MUX2_S0: TEENSY++.C1 (11), X.10 (S0)
MUX2_S1: TEENSY++.C0 (10), X.11 (S1)
MUX2_S2: TEENSY++.E1 (9), X.14 (S2)
MUX2_S3: TEENSY++.E0 (8), X.13 (S3)
MUX2_SIG: TEENSY++.F2 (40,A2), X.1 (COM)
MUX3_S0: TEENSY++.C5 (15,PWM), Y.10 (S0)
MUX3_S1: TEENSY++.C4 (14,PWM), Y.11 (S1)
MUX3_S2: TEENSY++.C3 (13), Y.14 (S2)
MUX3_S3: TEENSY++.C2 (12), Y.13 (S3)
MUX3_SIG: TEENSY++.F3 (41,A3), Y.1 (COM)
MUX4_S0: BUTTONS.10 (S0), TEENSY++.B3 (23)
MUX4_S1: BUTTONS.11 (S1), TEENSY++.B2 (22)
MUX4_S2: BUTTONS.14 (S2), TEENSY++.B1 (21)
MUX4_S3: BUTTONS.13 (S3), TEENSY++.B0 (20)
MUX4_SIG: BUTTONS.1 (COM), TEENSY++.F4 (42,A4)
unnamed: LED1.C, R12.1
OE: BLUE_DRIVER.23 (#OE), ORANGE_DRIVER.23 (#OE), R9.1, R35.1
O_A0: ORANGE_DRIVER.1 (A0), R34.2, SJ_A6.2
O_A1: ORANGE_DRIVER.2 (A1), R33.2, SJ_A7.2
O_A2: ORANGE_DRIVER.3 (A2), R32.2, SJ_A8.2
O_A3: ORANGE_DRIVER.4 (A3), R31.2, SJ_A9.2
O_A4: ORANGE_DRIVER.5 (A4), R30.2, SJ_A10.2
O_A5: ORANGE_DRIVER.24 (A5), R29.2, SJ_A11.2
PWRIN: J2.PWR, Q1.3 (D)
SCL: BLUE_DRIVER.26 (SCL), I2C.2, ORANGE_DRIVER.26 (SCL), R1.P$1 (1), R11.1, R37.1, TEENSY++.D0 (0,PWM,INT0)
SDA: BLUE_DRIVER.27 (SDA), I2C.1, ORANGE_DRIVER.27 (SDA), R2.P$2 (2), R10.1, R36.1, TEENSY++.D1 (1,PWM,INT1)
VCC: TEENSY++.5V (VCC)

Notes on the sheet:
Reverse voltage
protection
1 + A5 + A4 + A3 + A2 + A1 +A1 + RW
I2C Address =
Open = 0 / Closed = 1
MODULES
MUXES
ENCODER

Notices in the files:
parts and their libraries:
SparkFun-Connectors: Licensing: Creative Commons ShareAlike 4.0 International - https://creativecommons.org/licenses/by-sa/4.0
teensypp: Licensed Under Creative Commons Attribution-ShareAlike 3.0 Unported
teensypp: Licensed Under Creative Commons Attribution-ShareAlike 3.0 Unported (CC BY-SA 3.0)
